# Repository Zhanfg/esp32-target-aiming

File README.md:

# esp32-target-aiming

ESP32-S3 上的本地视觉目标锁定系统。摄像头找到目标，单片机算角度和轨迹，驱动双轴电机舵盘
把目标压回画面中心。

上位机只在开发期用，负责算法验证和标定。运行时不参与。

## 硬件

| 部件 | 选型 |
|---|---|
| 主控 | ESP32-S3 N16R8（16MB Flash / 8MB PSRAM） |
| 摄像头 | OV2640（主）/ OV5640（备） |
| 电机 ×2 | JGB37-520 12V 有刷减速电机，带霍尔编码器 |
| 驱动 | TB6612FNG 双路 H 桥，一片驱两轴 |
| 反馈 | ESP32 PCNT 硬件正交解码，四倍频 |
| 发射器 | 抽象接口 + 占位实现，型号待定 |
| 工具链 | VSCode + PlatformIO，C++17 |

## 目录

```
esp32-target-aiming/
├─ 00_MASTER_SPEC/      规格书与统一架构方案
├─ 01_PRIOR_ART/        现有来源与专利梳理
├─ 02_REQUIREMENTS/     方案设计、标定推导、硬件接线
├─ 03_CAD/              MST-01A ~ E 结构模型
├─ 04_SIMULATION/       准静态、瞬态、参数扫描
├─ 05_FIRMWARE/         ESP32-S3 固件、算法参考实现、I/O 映射
├─ 06_BOM/              物料清单
├─ 07_EXPERIMENTS/      工具链与 A ~ E 实验
├─ 08_DATA/             实验原始数据
├─ 09_PLOTS/            结果图表
├─ 10_FAILURE_ANALYSIS/ 失效分析
└─ 11_PUBLICATION_NOTES/ 论文与专利记录
```

依赖方向单向向下：`main → control → hal`，`vision` / `calibration` / `comms` 只依赖
`aim_types`，`math` 是公共底座。细节见 [02_REQUIREMENTS/方案设计.md](02_REQUIREMENTS/方案设计.md)。

## 几个设计取舍

先在 PC 上用 Python 把算法跑通再移植到单片机。参数在板子上盲调，出了问题分不清是算法错
还是传感器噪声大。

角度比较一律走 `angle_utils` 的环绕分支。现在按 ±180° 限位，将来换滑环做 360° 连续旋转时
控制算法不用重写。

提前量按执行机构滞后算。激光直瞄没有弹丸飞行时间，前视时间只由三部分组成：驱动延迟、
机械稳定时间、剩余角度除以最大角速度。

发射器需要显式 armed 且处于锁定态才允许触发，急停无条件生效。

## 当前状态

| 阶段 | 内容 | 状态 |
|---|---|---|
| P0 | 仓库骨架、PlatformIO 工程 | 进行中 |
| P1 | 标定层（内参 / 畸变 / 像素↔角度） | 待开始 |
| P2 | 算法核心与 PC 验证 | 进行中 |
| P3 | 视觉流水线 | 待开始 |
| P4 | 电机闭环控制 | 待开始 |
| P5 | 整机标定与精度评估 | 待开始 |
| P6 | 交付文档 | 待开始 |

阶段划分与验收指标见 [02_REQUIREMENTS/方案设计.md](02_REQUIREMENTS/方案设计.md) 第 11 节。

## 安全

这套东西含电机驱动机构和发射器接口。

上电前对照实物原理图核对 `05_FIRMWARE/include/config.h` 里的全部引脚。电机和逻辑分开供电、
单点共地，电机侧并一个 470µF 以上的电解电容。

电机铭牌上的减速比和编码器 PPR 要如实填进配置。这两个数字填错，整条角度链会按比例偏，
而且症状不直观。

发射器相关代码在完成安全评审前不要接真实装置。

## 文档

- [方案设计](02_REQUIREMENTS/方案设计.md)：架构、坐标系约定、算法公式、双环 PID、实施计划与验收标准
- [标定与几何推导](02_REQUIREMENTS/标定与几何推导.md)：针孔模型、畸变与反畸变迭代、像素↔角度互逆性证明、仿射最小二乘、精度预算
- [硬件接线与选型](02_REQUIREMENTS/硬件接线与选型.md)：BOM、引脚分配表、供电与接地、TB6612 真值表、上电检查清单

## 许可

MIT，见 [LICENSE](LICENSE)。

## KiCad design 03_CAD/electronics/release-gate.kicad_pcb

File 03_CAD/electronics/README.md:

# MST-01 释放门控电路板（release-gate）

本目录是释放路径的硬件门控板。它把统一架构方案 §6.6 的与门树、§6.5 的 H1/H2/H3/H4/H6
做成实体电路，让固件即使卡死或输出错误电平，也放不出一次释放。对应主规格 §10.3 的
`RELEASE_CMD` 输出与 §11 的四条互锁。

架构 §6.11 第一条说得很直接：这条不通过，后面所有状态机都是纸面。所以本板的设计重点不在
控制精度，而在每一个输入的失效方向，以及一块被卡住的 MCU 能造成什么。

信号极性和接口以 `02_REQUIREMENTS/interfaces.md` 第 5 节为准，引脚沿用
`05_FIRMWARE/include/config.h` 的 `RELEASE_CMD_PIN`、`STAGE1_STATE_PIN`、`STAGE2_STATE_PIN`
等定义。两者不一致时以接口文档为准，本板按接口文档的电平做。

## 1. 文件与用途

| 文件 | 用途 |
|---|---|
| `README.md` | 本文：设计说明、逻辑推导、极性表、H1 到 H6 落点、单点失效分析 |
| `release-gate.kicad_sch` | 原理图，KiCad 10 S-expression，含完整网表 |
| `release-gate.kicad_pcb` | 板图初版：外形、安装孔、布局、网表、地平面、执行链局部走线 |
| `release-gate.kicad_pro` / `.kicad_prl` | KiCad 打开时自动生成的工程文件 |
| `release-gate-schematic.pdf` / `.svg` | 原理图导出，供快速查看 |
| `release-gate-pcb.pdf` / `.svg` | 板图导出 |
| `bom.csv` | 物料清单，含位号、型号、数量、封装、作用 |
| `test-procedure.md` | 板级验证步骤，搭板后照做 |

本板不承担 H5（超出机械限位）。H5 由结构件上的物理止挡实现，见 `03_CAD` 各机型的结构件。

## 2. 供电与地

板上有两条供电，进板后各自串自恢复保险丝和防反：

- 逻辑轨 `+3V3`：从主控逻辑电源引入，经 `D14`（SS14 防反）与 `F1`（MF-MSMF050）。
  供五片 74HC、上拉/下拉和继电器（本版无继电器）。
- 执行轨 `V_ACT_IN`：从舵机与执行器电源引入，先过 `J7` 上的急停常闭触点变成 `V_ACT_SW`，
  再经 `F2`（MF-MSMF200）到释放电磁铁，另经 `F3`（MF-MSMF110）到预载执行器。
- 单点共地。逻辑地与执行地在板上汇到同一块铺铜，不另做隔离，避免地环路。

急停之后才出现 `V_ACT_SW`，这一点让急停独立于任何逻辑元件。后面所有 MOS 开关都只能
在 `V_ACT_SW` 存在时给执行器供电。

## 3. 与门树

### 3.1 逻辑表达式

```
Q1 = FIRE_INHIBIT_N · EXTERNAL_ALLOW · MECH_RECOVERED_N · POCKET_OR_MODE_A
Q2 = Q1 · ARMED_LATCH · RELEASE_PULSE · MASTER_ENABLE_GATED
MASTER_ENABLE_GATED = MASTER_ENABLE_RAW · FAULT_OK
FAULT_OK            = NOT(FAULT_LATCH)
POCKET_OR_MODE_A    = POCKET_ALIGNED OR MODE_A_RAW
```

Q2 经 `R22` 驱动低边 MOSFET `M1` 的栅极。M1 导通，释放电磁铁才通电；Q2 为低或悬空时 M1
关断。整条链上任何一级为假，释放都不可能发生。

### 3.2 器件选择

工程实践里做四输入与门，直接用一片 74HC21 最省。74HC21 是双 4 输入与门，一片正好给出
Q1 和 Q2 两级，不需要用 74HC08 拼树，也不用二极管与门凑，输入数、门数、传播延迟都对得上。
逻辑轨 3.3V，74HC 系列在 3.3V 下的输入阈值和驱动能力都够用。

其余逻辑按功能配：

- `U2` 74HC123：双可重触发单稳态，一半做释放脉宽钳位，一半做归零复位脉冲。
- `U3` 74HC74：双 D 触发器，一半做故障锁存，一半做武装锁存，异步置位/复位正好用来接
  故障置位和归零复位。
- `U4` 74HC11：三 3 输入与门，做三处 HOME 的与、武装时钟门、取消武装逻辑。
- `U5` 74HC14：六施密特反相器，做极性取反和慢边沿整形。
- `U6` 74HC08：四 2 输入与门，把故障锁存输出接进主使能和预载使能。

### 3.3 输入极性与开路行为

每个输入都按“开路即禁止”配偏置。外部上拉或下拉只是并上去，板端自己的偏置保证接插件
松脱、断线、掉电时落到禁止侧。执行器电源上的急停触点另算，它断的是功率。

| 信号 | 有效方向 | 板端偏置 | 开路结果 | 落点 |
|---|---|---|---|---|
| `FIRE_INHIBIT_N` | 高 = 未否决 | `R1` 10k 下拉，`R2` 串联 10k，`C1` 100n | 拉到低 | 否决，Q1 为假 |
| `EXTERNAL_ALLOW` | 高 = 许可 | `R3` 10k 下拉，`R4` 串联 10k，`C2` 100n | 拉到低 | 拒绝，Q1 为假 |
| `MECH_RECOVERED_RAW` | 低 = 机构已复位 | `R7` 10k 上拉，`C4` 100n | 拉到高 | 经 `U5A` 反相为低，Q1 为假 |
| `POCKET_ALIGNED` | 高 = 载荷对齐 | `R5` 10k 下拉，`R6` 串联 10k，`C3` 100n | 拉到低 | 对齐不满足，Q1 为假 |
| `MODE_A_RAW` | 高 = 模式 A 旁路 | 经 `JP1` 与外部常闭触点，`R27` 100k 下拉 | 拉到低 | 撤销旁路，退回要求真实对齐 |
| `ARM_CMD` | 高 = 请求武装 | `R8` 10k 下拉，`C5` 100n | 拉到低 | 不武装 |
| `DISARM_CMD` | 高 = 取消武装 | `R9` 10k 下拉，`C6` 100n | 拉到低 | 不取消，见 3.4 |
| `FAULT_CMD` | 高 = 软件请求故障 | `R10` 10k 下拉，`C7` 100n | 拉到低 | 不置故障，见 3.4 |
| `MCU_RELEASE_CMD` | 高 = 释放请求 | `R12` 10k 下拉，`R11` 串联 1k，`C8` 100n | 拉到低 | 无请求 |
| `MASTER_ENABLE_RAW` | 高 = 主使能有效 | `R18` 10k 下拉，`C13` 100n，且串急停触点 | 拉到低 | Q2 为假 |
| `PAN_HOME` / `TILT_HOME` / `MAG_HOME` | 高 = 已触发 | `R15` / `R16` / `R17` 10k 下拉，`C10` 到 `C12` 100n | 拉到低 | 视为未归零，故障锁存不能复位 |

`FIRE_INHIBIT_N` 与 `EXTERNAL_ALLOW` 的静态偏置在接口文档里规定为外部 10k 下拉，板端再各
并一只下拉，断线时两处都往低走。

### 3.4 两处不落到禁止侧但可接受的开路

`FAULT_CMD` 与 `DISARM_CMD` 开路时都拉到低。低电平分别表示“不置故障”和“不取消武装”。
两者都不是禁止侧电平，但它们本身只是软件发起的动作请求，缺失不会让释放更容易发生：
置故障是让系统更安全，取消武装也只是把武装锁存清零。真正的拦截已经由
`FIRE_INHIBIT_N`、`EXTERNAL_ALLOW`、`MASTER_ENABLE_RAW` 和故障锁存承担。这里如实标出，
免得把“开路即禁止”一概而论。

## 4. 单稳态钳时

### 4.1 电路

`MCU_RELEASE_CMD` 从 `J3` 进来，串 `R11`、对地 `C8`，接到 `U2A` 的 B 触发端（引脚 2）。
`U2A` 的 A 端（引脚 1）接 `GND`，使上升沿触发；`CLR`（引脚 3）接 `+3V3`。输出 Q（引脚 4）
是 `RELEASE_PULSE`，接到 Q2 的一个输入。RC 定时网络是 `R19` 与 `C15`，分别接在
`1REXT`（引脚 7）与 `1CEXT`（引脚 6）。

GPIO 直连的长驱动不再存在，释放命令必须先过这一级。MCU 把 `RELEASE_CMD` 拉高并保持，
单稳只输出一个固定宽度的脉冲，之后回到低，不会持续通电。

### 4.2 脉宽计算

74HC123 的脉宽按数据手册：

```
t_W ≈ K · R_EXT · C_EXT
```

其中 `K` 在 `C_EXT ≥ 1000 pF`、`VCC = 3.3V` 附近典型值约 1.0。取

- `R19 = 33 kΩ`，`C15 = 1 µF`，得 `t_W ≈ 33 ms`。

固件侧的软件脉宽是 `RELEASE_PULSE_MS = 30 ms`。硬件上限略大于软件脉冲，正常工作时由软件
结束释放，硬件不截断；MCU 卡在输出高时，硬件在约 33 ms 后强制关断。两侧都留了容差，实际
脉宽受电容容差（约 ±10%）、电阻容差和 `K` 的温度漂移影响，台架上用示波器测 `RELEASE_PULSE`
实测宽度，按结果微调 `C15`。执行器若需要更长动作时间，加大 `C15` 后重新验证。

`U2B` 用同样的公式做归零复位脉冲：`R20 = 22 kΩ`，`C16 = 1 µF`，得约 22 ms。

单稳是可重触发的。MCU 卡高只给一个上升沿，所以是一个脉冲；固件在释放脉冲有效期内不得
再次翻转 `RELEASE_CMD`，否则会把脉冲续长，这一条写进固件约束。

## 5. 负载开关

释放电磁铁的回流路径上串低边 N 沟道 MOSFET `M1`（AO3400A，SOT-23）：

- 栅极由 `Q2_OUT` 经 `R22`（100Ω）驱动，栅源之间有 `R21`（100k）下拉。Q2 悬空或走线断开时
  `R21` 把栅极拉到 `GND`，M1 关断。
- 漏极接 `EMAG_LO`（电磁铁回流端），源极接 `GND`。
- 电磁铁两端反并 `D1`（SS34），阴极朝 `EMAG_HI`，关断瞬间给感性电流一条续流回路。
- `V_ACT_SW` 到 `EMAG_HI` 之间串 `F2`（MF-MSMF200 自恢复保险丝），短路或堵转时限流。
- `V_ACT_SW` 对地挂 `D13`（SMBJ16A）做瞬态钳位。

预载执行器走同样结构：`M2` 栅极由 `PRELOAD_ENABLE` 驱动并带 `R23` 下拉，漏极 `PRELOAD_RET`
接 `J4` 的 2 脚。它的源极在板上不直接接地，改从 `J4` 的 3 脚 `MECH_RET` 引出，装机时把
机构常闭触点串进去再回地。机构未复位，触点断开，预载执行器在物理上没有回流路径。

## 6. 故障锁存器

### 6.1 电路

故障锁存用 `U3A`（74HC74 的一半）：

- 置位 `/1S`（引脚 4）接 `FAULT_SET_N`，由 `R29` 上拉，被 `U5E`（`FAULT_CMD` 反相）或
  急停辅助触点（`J7` 的 5、6 脚，常开对地）拉低时置位。
- 复位 `/1R`（引脚 1）接 `FAULT_RESET_N`，由 `R30` 上拉，被 `U2B` 的 `/Q`（引脚 13）
  或上电复位网络拉低时清零。
- 输出 `Q`（引脚 5）是 `FAULT_LATCH`，高表示故障已锁存并且保持。

`FAULT_LATCH` 经 `U5B` 取反成 `FAULT_OK`。`FAULT_OK` 进 `U6A`，与 `MASTER_ENABLE_RAW` 相与
得到 `MASTER_ENABLE_GATED`，作为 Q2 的一个输入；同时进 `U6B`、`U6D`，与 `PRELOAD_CMD`、
`MECH_RECOVERED_N` 相与得到 `PRELOAD_ENABLE`。故障一旦锁存，主使能被切断，预载也使能被切断。

### 6.2 为什么必须重新归零由电路保证

复位脉冲不是简单地把三处 HOME 相与。三处 HOME 先进 `U4A` 得到 `HOME_AND`，再送 `U2B` 的
B 端。`U2B` 只在 `HOME_AND` 的上升沿触发一次，输出一个约 22 ms 的低脉冲去清零 `U3A`。

这样处理有两个后果。机构停在非零位时 `HOME_AND` 为低，故障清不掉；要把三轴都驱动到参考
开关并同时触发，才会出现一次上升沿。如果故障发生时机构恰好已经停在三处零位，`HOME_AND`
没有边沿，锁存同样清不掉，必须先离开零位再重新归零。复位只发生在物理归零完成的瞬间，
软件无法凭一个 GPIO 把锁存清掉。

上电复位由 `R28`、`C14` 产生 `POR_N`，通过 `D11`、`D12` 分别接 `FAULT_RESET_N` 与
`ARM_RESET_N`，保证上电时两个锁存都从清零态开始，直到第一次真实归零。

## 7. 急停

急停用常闭蘑菇头，三个触点全部走 `J7`，不经过 MCU：

- 触点一（`J7` 1、2 脚）：串在执行轨里，`V_ACT_IN` 与 `V_ACT_SW` 之间。按下就断开执行轨，
  释放电磁铁和预载执行器同时失去供电。这条对应 H6。
- 触点二（`J7` 3、4 脚）：串在 `MASTER_KEY` 与 `MASTER_ENABLE_RAW` 之间。按下就让 Q2 的
  主使能输入变低。
- 触点三（`J7` 5、6 脚）：常开对地，按下时把 `FAULT_SET_N` 拉低，故障锁存置位。

按一次急停，执行轨断电、主使能断开、故障锁存置位三件事同时发生，而且都不依赖固件。

## 8. 模式 A 旁路

供给盘相关的对齐信号在模式 A 用旁路成真。旁路用外部常闭触点加焊接跳线 `JP1` 实现，
不靠继电器吸合直接给信号：

- `J6` 提供 `+3V3`（1 脚）、`MODE_A_SW`（2 脚）、`GND`（3 脚）。装机时把供给盘不在位时
  闭合的常闭触点接在 1、2 脚之间。
- `MODE_A_SW` 经 `JP1` 到 `MODE_A_RAW`，再由 `D7` 与 `POCKET_ALIGNED`（经 `D8`）做二极管或，
  节点 `POCKET_OR_MODE_A` 用 `R26` 100k 下拉后进 Q1。
- 供给盘没装时触点闭合，`MODE_A_RAW` 被拉高，旁路成立，模式 A 可以动作。装上盘后触点断开，
  `R27` 把 `MODE_A_RAW` 拉到低，旁路撤销，必须 `POCKET_ALIGNED` 为高才放行。默认状态落在
  模式 A 无载荷这一侧，符合架构 §6.5 的 H3。

需要跑模式 B 时把 `JP1` 拔掉，旁路彻底失效，只认对齐传感器。这一步写进模式 B 的作业流程。
另外要说明，如果供给盘实际已装但常闭触点卡在闭合，旁路会误成立，属于单点失效，见第 11 节。

## 9. ARMED_LATCH

`ARMED_LATCH` 由硬件锁存给出，用 `U3B`（74HC74 的另一半），不是 MCU 的普通 GPIO。

理由是架构 §6.9 第 8 条已经指出纯软件武装是缺陷。若武装只由一个 GPIO 表示，卡住的 MCU
可以直接把它拉高，与门树就少了一道。做成硬件锁存后，武装有三个条件同时满足才会成立：

```
ARM_CLK = Q1_OUT · ARM_CMD        （U4B 输出）
```

`ARM_CLK` 接到 `U3B` 的时钟端（引脚 11），`D` 端（引脚 12）接 `+3V3`，所以时钟上升沿把
`ARMED_LATCH` 置高并保持。要出现这个上升沿，`Q1_OUT` 必须已经为真，也就是外部许可、
安全否决、机构复位、对齐这几路全部成立，同时 MCU 给一次 `ARM_CMD`。MCU 单独把 `ARM_CMD`
钉在高不会重复置位，因为 `U3B` 是边沿触发。

清零走 `ARM_RESET_N`（`U4C` 输出）：

```
ARM_RESET_N = FAULT_OK · REL_IDLE · DISARM_CMD_OK
REL_IDLE    = NOT(RELEASE_PULSE)
```

故障锁存置位、一次释放脉冲结束、或 MCU 给 `DISARM_CMD`，都会把武装锁存清掉。这样一次
武装对应一次释放，发完自动回到未武装。上电由 `D12` 把 `ARM_RESET_N` 拉低清零。

## 10. H1 到 H6 的落点

| 硬约束 | 在本板上的落点 |
|---|---|
| H1 释放能量路径受多重条件约束 | `U1`（74HC21）构成 Q1 与 Q2 两级与门；`U2A` 把释放命令钳成单脉冲；`M1` 低边开关串回流路径；`F2` 限流；急停触点串执行轨。Q2 为假时 M1 关断 |
| H2 机构未复位时预载无法驱动 | `M2` 源极不接板地，经 `J4` 3 脚引到机构常闭触点再回地，触点断开时物理断路；逻辑上再经 `U6B`、`U6D` 与 `MECH_RECOVERED_N` 相与 |
| H3 模式 B 未对齐时释放无法完成 | `POCKET_ALIGNED` 经 `D8` 进 Q1；模式 A 由 `J6` 常闭触点加 `JP1`、`D7` 旁路，默认落在无载荷一侧 |
| H4 故障与急停锁存，未重新归零不能复位 | `U3A` 故障锁存；复位由 `U2B` 对 `HOME_AND` 上升沿的单稳脉冲驱动；锁存输出经 `U6A`、`U6B` 切主使能与预载 |
| H5 超出机械限位 | 本板不承担，由结构件物理止挡实现 |
| H6 主电源急停 | `J7` 的常闭触点直接串 `V_ACT` 与主使能键路，不经 MCU；辅助触点置故障锁存 |

## 11. 单点失效分析

下面列出会导致误释放的元件失效。误释放指在没有满足全部许可条件、或 MCU 不该发出释放时，
释放电磁铁仍被通电。

| 失效元件 | 失效方式 | 后果 | 板上是否有冗余或缓解 |
|---|---|---|---|
| `U2A`（74HC123） | 输出对 `+3V3` 短路或内部失效使 Q 恒高 | 时间钳位失效，只要 Q1、`ARMED_LATCH`、主使能成立就持续通电 | 无。缓解只能靠急停，建议改版加第二把串联器件或双单稳 |
| `M1`（AO3400A） | 漏源短路 | 不依赖栅极，`V_ACT_SW` 存在时电磁铁就通电 | 急停常闭触点串在 `V_ACT_SW` 之前，可断电；`F2` 只限流不切断 |
| `MOS_GATE_RELEASE` 走线 | 短到 `+3V3` | 绕过 Q2 使 M1 恒导通 | 急停可断电；建议改版在栅极串第二只受主使能控制的器件 |
| `U6A`（74HC08） | 输出卡高 | `MASTER_ENABLE_GATED` 恒高，故障锁存切不断主使能 | 无自动缓解，只能重新上电走 POR |
| `U5B`（74HC14） | 输出卡高使 `FAULT_OK` 恒高 | 故障切不断主使能与预载 | 无自动缓解 |
| `FIRE_INHIBIT_N` 线 | 短到 `+3V3` | 安全否决失效（对应 FM-08） | 板上无。需要架构 §6.7 提的双冗余触点交叉校验，本版留了位置未做 |
| `POCKET_ALIGNED` 线 | 短到 `+3V3` | 对齐失效，模式 B 可放出未对齐载荷 | 拔掉 `JP1` 不能阻止这一个，仍需双通道 |
| `MECH_RECOVERED_RAW` 线 | 短到 `GND` | 被当成已复位，Q1 与预载逻辑都放行 | 无。断线方向是安全的，短到地是危险方向 |
| `EXTERNAL_ALLOW` 线 | 短到 `+3V3` | 伪许可 | 无，需双通道 |
| `JP1` 与供给盘触点 | 盘已装但触点卡在闭合 | 模式 B 下旁路对齐 | 模式 B 流程要求拔掉 `JP1`，可消除这一条 |
| `U4C`（74HC11） | 输出卡高使 `ARM_RESET_N` 恒高 | 故障后武装锁存清不掉，只能上电复位 | 不影响误释放，但削弱互锁，建议改版用两把器件 |

不会导致误释放的失效方向也列出，说明哪些地方失效是安全的：`U3B` 失电或卡低使武装不成立；
`U5A` 失效使 `MECH_RECOVERED_N` 为低；`U5C` 卡高使 `REL_IDLE` 为高只是不能清零武装；任一
输入下拉丢失让对应条件不成立。这些方向都落到不释放。

冗余现状：急停有两个独立触点分别断执行轨和断主使能，这一点是冗余的。故障复位要求物理
归零序列，不能由单个信号清掉。架构 §6.7 与 §6.6 提到的双通道冗余触点交叉校验、安全输入
短路到 3V3 的检出，本版没有实现，是本板需要补的最大缺口。安全完整性做到哪一级要由后续
试验确认，设计上先按双通道留位。

## 12. 连接器与对外接口

| 连接器 | 引脚 | 说明 |
|---|---|---|
| `J1` PWR_IN | 1 `V_ACT_IN`，2 `+3V3`，3、4 `GND` | 电源输入 |
| `J2` ACT_OUT | 1 `EMAG_HI`，2 `EMAG_LO`，3 `GND` | 释放电磁铁 |
| `J3` SAFETY_IN | 20 脚，含 `FIRE_INHIBIT_N`、`EXTERNAL_ALLOW`、`MECH_RECOVERED_RAW`、`POCKET_ALIGNED`、`ARM_CMD`、`DISARM_CMD`、`FAULT_CMD`、`MCU_RELEASE_CMD`、`PRELOAD_CMD` 与多地 | 安全与控制输入 |
| `J4` PRELOAD_OUT | 1 `PRELOAD_HI`，2 `PRELOAD_RET`，3 `MECH_RET` | 预载执行器，3 脚外接机构常闭触点回地 |
| `J5` HOME | 1 `PAN_HOME`，2 `TILT_HOME`，3 `MAG_HOME`，4 `GND` | 三处参考开关 |
| `J6` MODE_MAG | 1 `+3V3`，2 `MODE_A_SW`，3 `GND` | 供给盘在位常闭触点 |
| `J7` ESTOP | 1、2 执行轨；3、4 主使能；5、6 故障置位 | 急停三触点 |
| `J8` KEY | 1 `+3V3`，2 `MASTER_KEY`，3 `GND` | 人工总开关或钥匙 |
| `J9` STATUS | `FAULT_LATCH`、`ARMED_LATCH`、`HOME_AND_N`、`Q2_OUT`、`MECH_RECOVERED_RAW`、`MECH_RECOVERED_N`、`READY_DIAG`、`GND` | 状态回主控，注意 `HOME_AND_N` 是反相后的低有效 |

`J9` 的 `Q2_OUT` 可以让固件读到释放门此刻是否被打通，作为软件自检之外的第二路确认。
`MECH_RECOVERED_RAW` 直接引回主控的 MCP23017 输入位 6，板上同时用它和它反相后的
`MECH_RECOVERED_N`，方向与接口文档 §3.2 一致（原始位低表示已复位）。

## 13. KiCad 生成与验证状态

本机安装了 KiCad 10.0.5，命令行 `kicad-cli` 与 `pcbnew` 的 Python 模块可用。我没有可用的
`kicad_*` MCP 工具，所以原理图与 PCB 是用脚本调用 KiCad 的 Python 接口和文本格式生成的，
不是纯手写后没经过任何工具。

实际跑过的验证：

| 项目 | 命令 | 结果 |
|---|---|---|
| 原理图网表 | `kicad-cli sch export netlist` | 成功，97 个符号实例（含 2 个 ERC 电源旗标，实际采购件 95 个）、60 个网络，逻辑节点与本文一致 |
| 原理图 ERC | `kicad-cli sch erc --severity-all` | 0 条 error；97 条 `lib_symbol_issues` 警告，原因是内联符号库 `rg` 未注册进 `sym-lib-table`，不影响网表与显示 |
| 原理图导出 | `kicad-cli sch export pdf` / `svg` | 成功，PDF 与 SVG 已在本目录 |
| PCB DRC（自动布线前） | `kicad-cli pcb drc --severity-all` | 1 条丝印重叠警告；151 个未连接项来自信号布线尚未做完 |
| PCB DRC（自动布线并重灌铜箔后） | 同上 | 20 条违规（19 条线宽、1 条丝印）加 23 个未连接项。详见第 14 节 |
| PCB 导出 | `kicad-cli pcb export pdf` / `svg` | 成功 |

说明两点。原理图的连接用贴在引脚端点的网络标签表达，不是逐段连线的画法，电气连接正确，
但观感上与手工画的图不同。PCB 是初版布局：外形、安装孔、去耦、地平面、执行器供电与栅极
驱动这几段已经布通，其余信号的铜线还没走完，所以 DRC 有 151 个未连接项。这些文件没有用
KiCad 图形界面逐屏人工检查过，上面的结论全部来自 `kicad-cli`。

## 14. 已知缺口与下一步

1. 双通道冗余触点与安全输入短路到 3V3 的检出尚未实现。这是 FM-08 与 §6.7 的缺口，也是
   本板最该先补的部分。
2. 信号布线已自动布通大半，但未干净。用 Freerouting 2.4.1（JAR 在 `~/.kicad-mcp/freerouting.jar`）
   自动布线，未连接项从 151 降到 23。管线是：`pcbnew.ExportSpecctraDSN` 导出 DSN、
   `java -jar freerouting.jar -de <dsn> -do <ses> --gui.enabled=false -mp 30` 布线、
   `pcbnew.ImportSpecctraSES` 回导、`pcbnew.ZONE_FILLER` 重灌铜箔。**重灌那一步不能省**，
   否则铜箔没避让新走线，DRC 会把 511 处报成短路。

   两个残留问题。一是线宽：DSN 里的规则写的是 `(width 200)`（0.2 mm），工程 netclass 也是 0.2 mm，
   但 Freerouting 实际用了 0.15 mm，留下 19 条线宽违规。二是 23 个未连接项，Freerouting 只报 2 条
   布不通，其余应该是重灌铜箔后不再靠铺铜糊住的连接。正式投板前这两项都要清掉。
3. 执行器电流尚未冻结。`M1`、`F2`、`D1` 的规格按中小电流电磁铁选的，执行器定型后按峰值
   电流与浪涌时间复核，必要时换更大封装的 MOSFET 和保险丝。
4. 归零复位脉宽与释放脉宽都要在台架实测后微调，见 `test-procedure.md`。
5. 本板按模式 A 默认安全侧设计。模式 B 的作业流程必须包含拔除 `JP1`,否则旁路会在盘已装
   时留下误释放通道。

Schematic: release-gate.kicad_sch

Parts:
C1, C2, C3, C4, C5, C6, C7, C8, C9, C10, C11, C12, C13, C14, C18, C19, C20, C21, C22, C23: 100n; C_0805_2012Metric
C15, C16: 1u; C_0805_2012Metric
C17: 10u; C_1206_3216Metric
D1: SS34; D_SMA
D7, D8: BAT54W; D_SOD-123
D9: GATE_OK; LED_0805_2012Metric
D10: FAULT; LED_0805_2012Metric
D11, D12: 1N4148W; D_SOD-123
D13: SMBJ16A; D_SMB
D14: SS14; D_SMA
F1: MF-MSMF050; Fuse_1206_3216Metric
F2: MF-MSMF200; Fuse_1812_4532Metric
F3: MF-MSMF110; Fuse_1206_3216Metric
J1: PWR_IN; PinHeader_1x04_P2.54mm_Vertical
J2: ACT_OUT; PinHeader_1x03_P2.54mm_Vertical
J3: SAFETY_IN; PinHeader_1x20_P2.54mm_Vertical
J4: PRELOAD_OUT; PinHeader_1x03_P2.54mm_Vertical
J5: HOME; PinHeader_1x04_P2.54mm_Vertical
J6: MODE_MAG; PinHeader_1x03_P2.54mm_Vertical
J7: ESTOP; PinHeader_1x06_P2.54mm_Vertical
J8: KEY; PinHeader_1x03_P2.54mm_Vertical
J9: STATUS; PinHeader_1x08_P2.54mm_Vertical
JP1: MODE_A_EN; SolderJumper-2_P1.3mm_Open_Pad1.0x1.5mm
M1, M2: AO3400A; SOT-23
PWR1, PWR2: PWR_FLAG
R1, R2, R3, R4, R5, R6, R7, R8, R9, R10, R12, R14, R15, R16, R17, R18, R29, R30, R31: 10k; R_0805_2012Metric
R11, R13, R24, R25: 1k; R_0805_2012Metric
R19: 33k; R_0805_2012Metric
R20: 22k; R_0805_2012Metric
R21, R23, R26, R27, R28, R32: 100k; R_0805_2012Metric
R22: 100; R_0805_2012Metric
TP1: FIRE_INHIBIT_N; TestPoint_Pad_D1.5mm
TP2: EXTERNAL_ALLOW; TestPoint_Pad_D1.5mm
TP3: MECH_RECOVERED_N; TestPoint_Pad_D1.5mm
TP4: POCKET_OR_MODE_A; TestPoint_Pad_D1.5mm
TP5: Q1_OUT; TestPoint_Pad_D1.5mm
TP6: Q2_OUT; TestPoint_Pad_D1.5mm
TP7: RELEASE_PULSE; TestPoint_Pad_D1.5mm
TP8: FAULT_LATCH; TestPoint_Pad_D1.5mm
TP9: HOME_AND; TestPoint_Pad_D1.5mm
TP10: MASTER_ENABLE_RAW; TestPoint_Pad_D1.5mm
U1: 74HC21; SOIC-14_3.9x8.7mm_P1.27mm
U2: 74HC123; SOIC-16_3.9x9.9mm_P1.27mm
U3: 74HC74; SOIC-14_3.9x8.7mm_P1.27mm
U4: 74HC11; SOIC-14_3.9x8.7mm_P1.27mm
U5: 74HC14; SOIC-14_3.9x8.7mm_P1.27mm
U6: 74HC08; SOIC-14_3.9x8.7mm_P1.27mm

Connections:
+3V3: C17.1, C18.1, C19.1, C20.1, C21.1, C22.1, C23.1, F1.2, J3.19, J6.1, J8.1, PWR1.1, R7.1, R19.1, R20.1, R28.1, R29.1, R30.1, R31.1, U1.14 (VCC), U2.3 (1CLR), U2.11 (2CLR), U2.16 (VCC), U3.10 (~2S), U3.12 (2D), U3.14 (VCC), U4.5 (2C), U4.14 (VCC), U5.14 (VCC), U6.14 (VCC)
+3V3_PRE: D14.1 (K), F1.1
+3V3_RAW: D14.2 (A), J1.2
ARMED_LATCH: J9.2, U1.10 (2B), U3.9 (2Q)
ARM_CLK: U3.11 (2C), U4.6 (2Y)
ARM_CMD: C5.1, J3.9, R8.1, U4.4 (2B)
ARM_RESET_N: D11.2 (A), R31.2, U3.13 (~2R), U4.8 (3Y)
C1T: C15.1, U2.6 (1CEXT)
C2T: C16.1, U2.14 (2CEXT)
DISARM_CMD: C6.1, J3.11, R9.1, U5.9 (4A)
DISARM_CMD_OK: U4.11 (3C), U5.8 (4Y)
EA_RAW: J3.3, R4.1
EMAG_HI: D1.1 (K), F2.2, J2.1
EMAG_LO: D1.2 (A), J2.2, M1.3 (D)
EXTERNAL_ALLOW: C2.1, R3.1, R4.2, TP2.1, U1.2 (1B)
FAULT_CMD: C7.1, J3.13, R10.1, U5.11 (5A)
FAULT_LATCH: J9.1, R25.1, TP8.1, U3.5 (1Q), U5.3 (2A)
FAULT_OK: U4.9 (3A), U5.4 (2Y), U6.2 (1B), U6.5 (2B), U6.9 (3A)
FAULT_RESET_N: D12.2 (A), R30.2, U2.13 (~2Q), U3.1 (~1R)
FAULT_SET_N: J7.5, R29.2, U3.4 (~1S), U5.10 (5Y)
FIRE_INHIBIT_N: C1.1, R1.1, R2.2, TP1.1, U1.1 (1A)
FI_RAW: J3.1, R2.1
GND: C1.2, C2.2, C3.2, C4.2, C5.2, C6.2, C7.2, C8.2, C9.2, C10.2, C11.2, C12.2, C13.2, C14.2, C17.2, C18.2, C19.2, C20.2, C21.2, C22.2, C23.2, D9.1 (K), D10.1 (K), D13.2 (A), J1.3, J1.4, J2.3, J3.2, J3.4, J3.6, J3.8, J3.10, J3.12, J3.14, J3.16, J3.18, J3.20, J5.4, J6.3, J7.6, J8.3, J9.8, M1.2 (S), PWR2.1, R1.2, R3.2, R5.2, R8.2, R9.2, R10.2, R12.2, R14.2, R15.2, R16.2, R17.2, R18.2, R21.2, R23.2, R26.2, R27.2, R32.2, U1.7 (GND), U2.1 (1A), U2.8 (GND), U2.9 (2A), U3.2 (1D), U3.3 (1C), U3.7 (GND), U4.7 (GND), U5.7 (GND), U6.7 (GND)
HOME_AND: R32.1, TP9.1, U2.10 (2B), U4.12 (1Y), U5.13 (6A)
HOME_AND_N: J9.3, U5.12 (6Y)
LED_FAULT_A: D10.2 (A), R25.2
LED_GATE_A: D9.2 (A), R24.2
MAG_HOME: C12.1, J5.3, R17.1, U4.13 (1C)
MASTER_ENABLE_GATED: U1.13 (2D), U6.3 (1Y)
MASTER_ENABLE_RAW: C13.1, J7.4, R18.1, TP10.1, U6.1 (1A)
MASTER_KEY: J7.3, J8.2
MCU_RELEASE_CMD: C8.1, R11.2, R12.1, U2.2 (1B)
MECH_RECOVERED_N: J9.6, TP3.1, U1.4 (1C), U5.2 (1Y), U6.10 (3B), U6.13 (4B)
MECH_RECOVERED_RAW: C4.1, J3.5, J9.5, R7.2, U5.1 (1A)
MECH_RET: J4.3, M2.2 (S)
MODE_A_RAW: D7.2 (A), JP1.2, R27.1
MODE_A_SW: J6.2, JP1.1
MOS_GATE_RELEASE: M1.1 (G), R21.1, R22.2
PAN_HOME: C10.1, J5.1, R15.1, U4.1 (1A)
PA_RAW: J3.7, R6.1
PL_CMD_RAW: J3.17, R13.1
POCKET_ALIGNED: C3.1, D8.2 (A), R5.1, R6.2
POCKET_OR_MODE_A: D7.1 (K), D8.1 (K), R26.1, TP4.1, U1.5 (1D)
POR_N: C14.1, D11.1 (K), D12.1 (K), R28.2
PRELOAD_CMD: C9.1, R13.2, R14.1, U6.4 (2A)
PRELOAD_CMD_GATED: U6.6 (2Y), U6.12 (4A)
PRELOAD_ENABLE: M2.1 (G), R23.1, U6.11 (4Y)
PRELOAD_HI: F3.2, J4.1
PRELOAD_RET: J4.2, M2.3 (D)
Q1_OUT: TP5.1, U1.6 (1Y), U1.9 (2A), U4.3 (2A)
Q2_OUT: J9.4, R22.1, R24.1, TP6.1, U1.8 (2Y)
R1T: C15.2, R19.2, U2.7 (1REXT)
R2T: C16.2, R20.2, U2.15 (2REXT)
READY_DIAG: J9.7, U6.8 (3Y)
RELEASE_PULSE: TP7.1, U1.12 (2C), U2.4 (1Q), U5.5 (3A)
REL_CMD_RAW: J3.15, R11.1
REL_IDLE: U4.10 (3B), U5.6 (3Y)
TILT_HOME: C11.1, J5.2, R16.1, U4.2 (1B)
V_ACT_IN: J1.1, J7.1
V_ACT_SW: D13.1 (K), F2.1, F3.1, J7.2

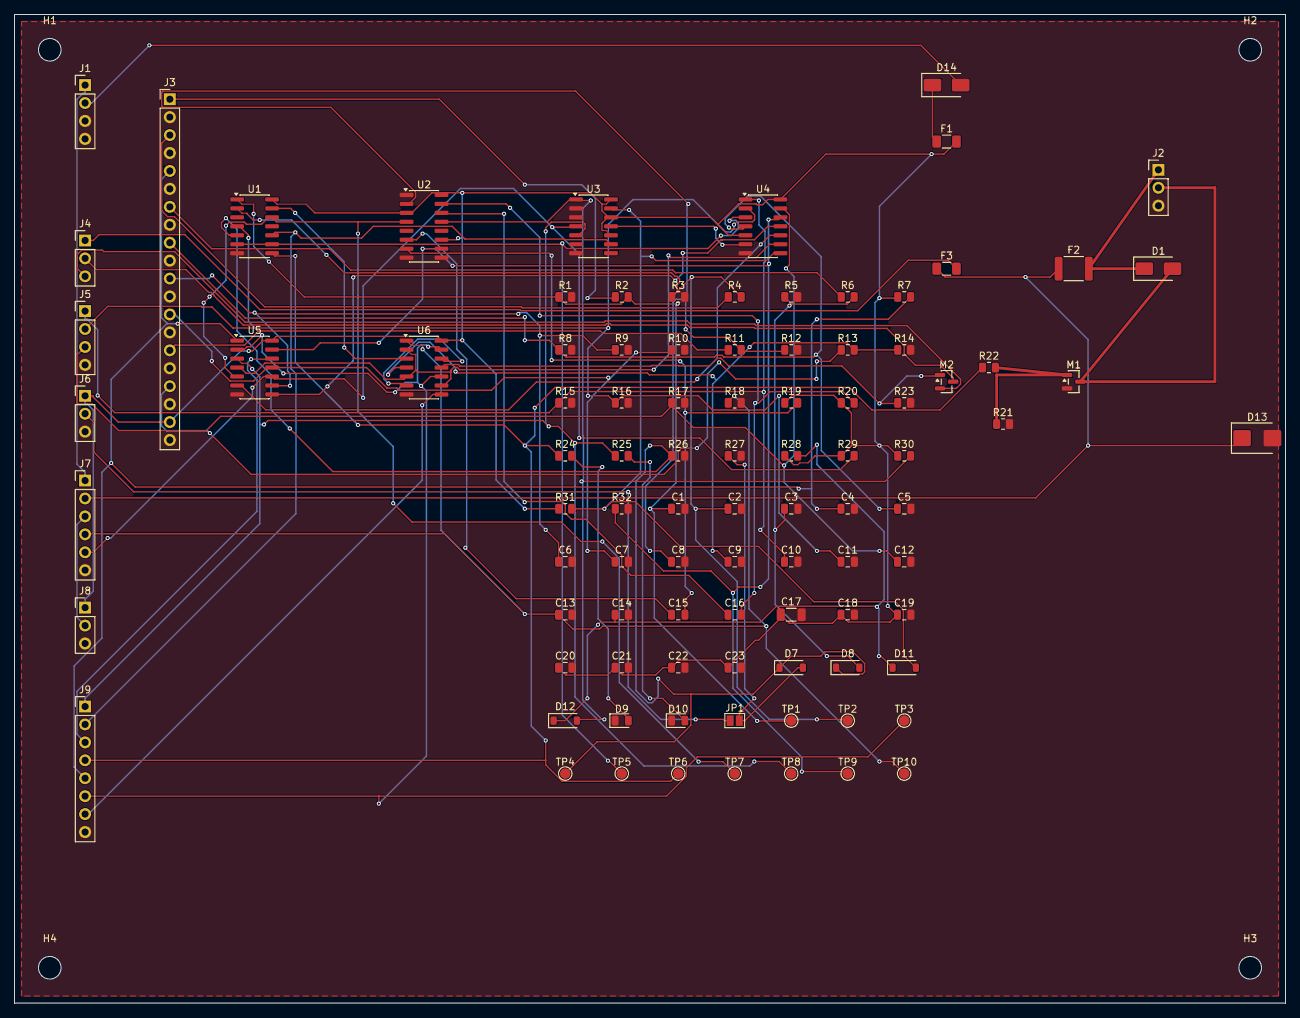
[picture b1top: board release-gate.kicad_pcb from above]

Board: 2 copper layers, 180.0 x 140.0 mm, 99 parts (0 on the bottom side), 60 nets.

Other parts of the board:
H1, H2, H3, H4: MountingHole; MountingHole_3.2mm_M3

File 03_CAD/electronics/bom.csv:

位号,型号,数量,封装,作用
R1,10k,1,Resistor_SMD:R_0805_2012Metric,FIRE_INHIBIT_N 下拉，开路即否决
R2,10k,1,Resistor_SMD:R_0805_2012Metric,FIRE_INHIBIT_N 串联限流
R3,10k,1,Resistor_SMD:R_0805_2012Metric,EXTERNAL_ALLOW 下拉，开路即拒绝
R4,10k,1,Resistor_SMD:R_0805_2012Metric,EXTERNAL_ALLOW 串联限流
R5,10k,1,Resistor_SMD:R_0805_2012Metric,POCKET_ALIGNED 下拉，开路即禁止
R6,10k,1,Resistor_SMD:R_0805_2012Metric,POCKET_ALIGNED 串联限流
R7,10k,1,Resistor_SMD:R_0805_2012Metric,MECH_RECOVERED_RAW 上拉，断线被反相器判为未复位
R8,10k,1,Resistor_SMD:R_0805_2012Metric,ARM_CMD 下拉，开路不武装
R9,10k,1,Resistor_SMD:R_0805_2012Metric,DISARM_CMD 下拉
R10,10k,1,Resistor_SMD:R_0805_2012Metric,FAULT_CMD 下拉
R11,1k,1,Resistor_SMD:R_0805_2012Metric,MCU_RELEASE_CMD 串联限流
R12,10k,1,Resistor_SMD:R_0805_2012Metric,MCU_RELEASE_CMD 下拉，开路无请求
R13,1k,1,Resistor_SMD:R_0805_2012Metric,PRELOAD_CMD 串联限流
R14,10k,1,Resistor_SMD:R_0805_2012Metric,PRELOAD_CMD 下拉，开路不预载
R15,10k,1,Resistor_SMD:R_0805_2012Metric,PAN_HOME 开关下拉，开路视为未归零
R16,10k,1,Resistor_SMD:R_0805_2012Metric,TILT_HOME 开关下拉，开路视为未归零
R17,10k,1,Resistor_SMD:R_0805_2012Metric,MAG_HOME 开关下拉，开路视为未归零
R18,10k,1,Resistor_SMD:R_0805_2012Metric,MASTER_ENABLE_RAW 下拉，开路即失能
R19,33k,1,Resistor_SMD:R_0805_2012Metric,单稳态定时电阻 R_EXT
R20,22k,1,Resistor_SMD:R_0805_2012Metric,单稳态定时电阻 R_EXT
R21,100k,1,Resistor_SMD:R_0805_2012Metric,MOSFET 栅极下拉（开路即关断）
R22,100,1,Resistor_SMD:R_0805_2012Metric,MOSFET 栅极串联电阻
R23,100k,1,Resistor_SMD:R_0805_2012Metric,MOSFET 栅极下拉（开路即关断）
R24,1k,1,Resistor_SMD:R_0805_2012Metric,串联限流/指示灯限流
R25,1k,1,Resistor_SMD:R_0805_2012Metric,串联限流/指示灯限流
R26,100k,1,Resistor_SMD:R_0805_2012Metric,POCKET_OR_MODE_A 下拉，两路都开路即禁止
R27,100k,1,Resistor_SMD:R_0805_2012Metric,MODE_A_RAW 下拉，装盘或断线即撤销旁路
R28,100k,1,Resistor_SMD:R_0805_2012Metric,POR 定时上拉
R29,10k,1,Resistor_SMD:R_0805_2012Metric,FAULT_SET_N 上拉
R30,10k,1,Resistor_SMD:R_0805_2012Metric,FAULT_RESET_N 上拉
R31,10k,1,Resistor_SMD:R_0805_2012Metric,ARM_RESET_N 上拉
R32,100k,1,Resistor_SMD:R_0805_2012Metric,HOME_AND 下拉，开路即无归零脉冲
C1,100n,1,Capacitor_SMD:C_0805_2012Metric,滤波或去耦
C2,100n,1,Capacitor_SMD:C_0805_2012Metric,滤波或去耦
C3,100n,1,Capacitor_SMD:C_0805_2012Metric,滤波或去耦
C4,100n,1,Capacitor_SMD:C_0805_2012Metric,滤波或去耦
C5,100n,1,Capacitor_SMD:C_0805_2012Metric,滤波或去耦
C6,100n,1,Capacitor_SMD:C_0805_2012Metric,滤波或去耦
C7,100n,1,Capacitor_SMD:C_0805_2012Metric,滤波或去耦
C8,100n,1,Capacitor_SMD:C_0805_2012Metric,滤波或去耦
C9,100n,1,Capacitor_SMD:C_0805_2012Metric,滤波或去耦
C10,100n,1,Capacitor_SMD:C_0805_2012Metric,滤波或去耦
C11,100n,1,Capacitor_SMD:C_0805_2012Metric,滤波或去耦
C12,100n,1,Capacitor_SMD:C_0805_2012Metric,滤波或去耦
C13,100n,1,Capacitor_SMD:C_0805_2012Metric,滤波或去耦
C14,100n,1,Capacitor_SMD:C_0805_2012Metric,滤波或去耦
C15,1u,1,Capacitor_SMD:C_0805_2012Metric,单稳态定时电容 C_EXT
C16,1u,1,Capacitor_SMD:C_0805_2012Metric,单稳态定时电容 C_EXT
C17,10u,1,Capacitor_SMD:C_1206_3216Metric,逻辑轨储能
C18,100n,1,Capacitor_SMD:C_0805_2012Metric,滤波或去耦
C19,100n,1,Capacitor_SMD:C_0805_2012Metric,滤波或去耦
C20,100n,1,Capacitor_SMD:C_0805_2012Metric,滤波或去耦
C21,100n,1,Capacitor_SMD:C_0805_2012Metric,滤波或去耦
C22,100n,1,Capacitor_SMD:C_0805_2012Metric,滤波或去耦
C23,100n,1,Capacitor_SMD:C_0805_2012Metric,滤波或去耦
D1,SS34,1,Diode_SMD:D_SMA,肖特基：释放电磁铁续流
D7,BAT54W,1,Diode_SMD:D_SOD-123,肖特基：模式A旁路与对齐信号的二极管或
D8,BAT54W,1,Diode_SMD:D_SOD-123,肖特基：模式A旁路与对齐信号的二极管或
D11,1N4148W,1,Diode_SMD:D_SOD-123,小信号：上电复位脉冲到两个锁存器
D12,1N4148W,1,Diode_SMD:D_SOD-123,小信号：上电复位脉冲到两个锁存器
D13,SMBJ16A,1,Diode_SMD:D_SMB,TVS：执行轨瞬态钳位
D14,SS14,1,Diode_SMD:D_SMA,肖特基：逻辑轨输入防反
D9,GATE_OK,1,LED_SMD:LED_0805_2012Metric,LED：释放门 Q2 使能指示
D10,FAULT,1,LED_SMD:LED_0805_2012Metric,LED：故障锁存指示
F1,MF-MSMF050,1,Fuse:Fuse_1206_3216Metric,自恢复保险丝：逻辑轨
F2,MF-MSMF200,1,Fuse:Fuse_1812_4532Metric,自恢复保险丝：执行轨
F3,MF-MSMF110,1,Fuse:Fuse_1206_3216Metric,自恢复保险丝：预载轨
M1,AO3400A,1,Package_TO_SOT_SMD:SOT-23,低边N沟道MOSFET：释放/预载执行器回流开关
M2,AO3400A,1,Package_TO_SOT_SMD:SOT-23,低边N沟道MOSFET：释放/预载执行器回流开关
JP1,MODE_A_EN,1,Jumper:SolderJumper-2_P1.3mm_Open_Pad1.0x1.5mm,焊接跳线：模式A旁路使能，默认闭合
U1,74HC21,1,Package_SO:SOIC-14_3.9x8.7mm_P1.27mm,双4输入与门：构成 Q1/Q2 与门树
U2,74HC123,1,Package_SO:SOIC-16_3.9x9.9mm_P1.27mm,双可重触发单稳态：钳释放脉冲宽度、产生归零复位脉冲
U3,74HC74,1,Package_SO:SOIC-14_3.9x8.7mm_P1.27mm,双D触发器：故障锁存器 U3A、武装锁存器 U3B
U4,74HC11,1,Package_SO:SOIC-14_3.9x8.7mm_P1.27mm,三3输入与门：HOME 与、武装时钟门、取消武装逻辑
U5,74HC14,1,Package_SO:SOIC-14_3.9x8.7mm_P1.27mm,六施密特反相器：MECH_RECOVERED 反相、故障/脉冲/命令取反、整形
U6,74HC08,1,Package_SO:SOIC-14_3.9x8.7mm_P1.27mm,四2输入与门：主使能与预载的故障门控
J1,PWR_IN,1,Connector_PinHeader_2.54mm:PinHeader_1x04_P2.54mm_Vertical,连接器：PWR_IN
J2,ACT_OUT,1,Connector_PinHeader_2.54mm:PinHeader_1x03_P2.54mm_Vertical,连接器：ACT_OUT
J3,SAFETY_IN,1,Connector_PinHeader_2.54mm:PinHeader_1x20_P2.54mm_Vertical,连接器：SAFETY_IN
J4,PRELOAD_OUT,1,Connector_PinHeader_2.54mm:PinHeader_1x03_P2.54mm_Vertical,连接器：PRELOAD_OUT
J5,HOME,1,Connector_PinHeader_2.54mm:PinHeader_1x04_P2.54mm_Vertical,连接器：HOME
J6,MODE_MAG,1,Connector_PinHeader_2.54mm:PinHeader_1x03_P2.54mm_Vertical,连接器：MODE_MAG
J7,ESTOP,1,Connector_PinHeader_2.54mm:PinHeader_1x06_P2.54mm_Vertical,连接器：ESTOP
J8,KEY,1,Connector_PinHeader_2.54mm:PinHeader_1x03_P2.54mm_Vertical,连接器：KEY
J9,STATUS,1,Connector_PinHeader_2.54mm:PinHeader_1x08_P2.54mm_Vertical,连接器：STATUS
TP1,FIRE_INHIBIT_N,1,TestPoint:TestPoint_Pad_D1.5mm,测试点：FIRE_INHIBIT_N
TP2,EXTERNAL_ALLOW,1,TestPoint:TestPoint_Pad_D1.5mm,测试点：EXTERNAL_ALLOW
TP3,MECH_RECOVERED_N,1,TestPoint:TestPoint_Pad_D1.5mm,测试点：MECH_RECOVERED_N
TP4,POCKET_OR_MODE_A,1,TestPoint:TestPoint_Pad_D1.5mm,测试点：POCKET_OR_MODE_A
TP5,Q1_OUT,1,TestPoint:TestPoint_Pad_D1.5mm,测试点：Q1_OUT
TP6,Q2_OUT,1,TestPoint:TestPoint_Pad_D1.5mm,测试点：Q2_OUT
TP7,RELEASE_PULSE,1,TestPoint:TestPoint_Pad_D1.5mm,测试点：RELEASE_PULSE
TP8,FAULT_LATCH,1,TestPoint:TestPoint_Pad_D1.5mm,测试点：FAULT_LATCH
TP9,HOME_AND,1,TestPoint:TestPoint_Pad_D1.5mm,测试点：HOME_AND
TP10,MASTER_ENABLE_RAW,1,TestPoint:TestPoint_Pad_D1.5mm,测试点：MASTER_ENABLE_RAW
